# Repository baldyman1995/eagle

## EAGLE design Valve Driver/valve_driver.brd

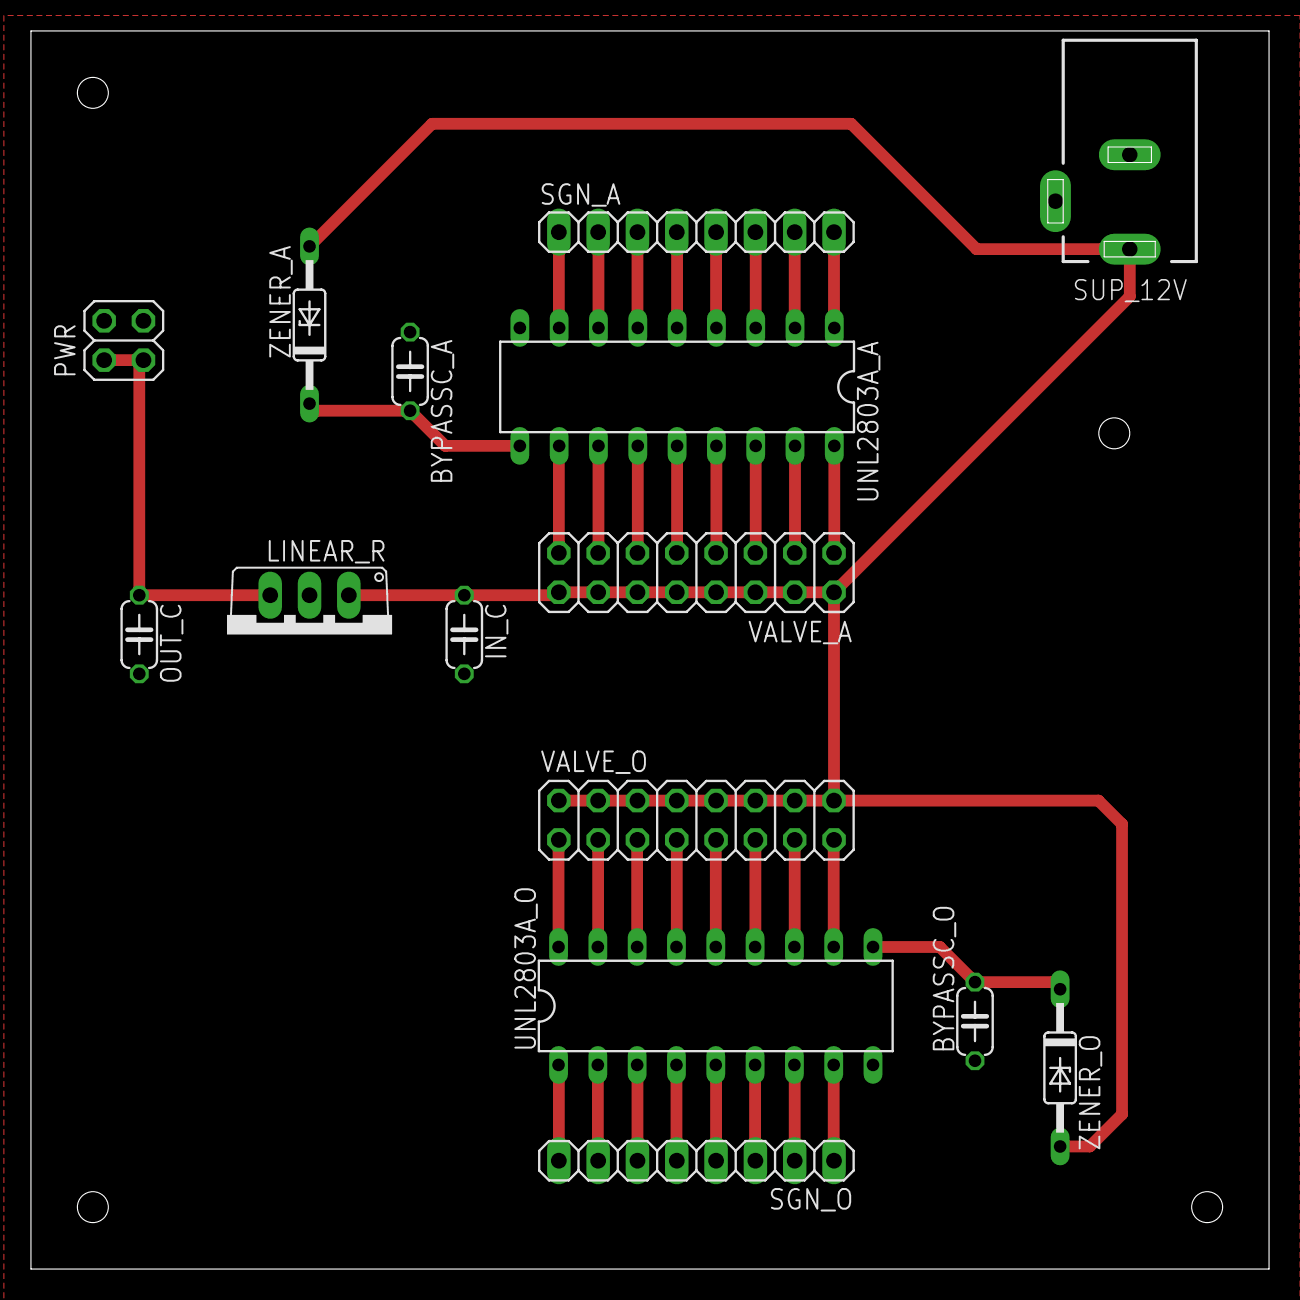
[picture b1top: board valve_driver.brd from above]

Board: 2 copper layers, 80.0 x 80.0 mm, 15 parts (0 on the bottom side), 37 nets.

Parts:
BYPASSC_A: 0.33u; C050-024X044
BYPASSC_O: 0.33u; C050-024X044
IN_C: 0.33u; C050-024X044
LINEAR_R: 7805TV; TO220V
OUT_C: 0.1u; C050-024X044
PWR: 2X02
SGN_A: 1X08
SGN_O: 1X08
SUP_12V: DCJ0202
UNL2803A_A, UNL2803A_O: DIL18
VALVE_A: 2X08
VALVE_O: 2X08
ZENER_A: 18v; DO35Z10
ZENER_O: 18v; DO35Z10

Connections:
COM1: BYPASSC_A.2, UNL2803A_A.10, ZENER_A.C
COM2: BYPASSC_O.2, UNL2803A_O.10, ZENER_O.C
GND: BYPASSC_A.1, BYPASSC_O.1, IN_C.2, LINEAR_R.2, OUT_C.2, PWR.3, PWR.4, SUP_12V.2, SUP_12V.3, UNL2803A_A.9, UNL2803A_O.9
unnamed: UNL2803A_O.11, VALVE_O.15
unnamed: UNL2803A_O.12, VALVE_O.13
unnamed: UNL2803A_O.13, VALVE_O.11
unnamed: UNL2803A_O.14, VALVE_O.9
unnamed: UNL2803A_O.15, VALVE_O.7
unnamed: UNL2803A_O.16, VALVE_O.5
unnamed: UNL2803A_O.17, VALVE_O.3
unnamed: UNL2803A_O.18, VALVE_O.1
unnamed: SGN_O.1, UNL2803A_O.8
unnamed: SGN_O.2, UNL2803A_O.7
unnamed: SGN_O.3, UNL2803A_O.6
unnamed: SGN_O.4, UNL2803A_O.5
unnamed: SGN_O.5, UNL2803A_O.4
unnamed: SGN_O.6, UNL2803A_O.3
unnamed: SGN_O.7, UNL2803A_O.2
unnamed: SGN_O.8, UNL2803A_O.1
unnamed: UNL2803A_A.11, VALVE_A.15
unnamed: UNL2803A_A.12, VALVE_A.13
unnamed: UNL2803A_A.13, VALVE_A.11
unnamed: UNL2803A_A.14, VALVE_A.9
unnamed: UNL2803A_A.15, VALVE_A.7
unnamed: UNL2803A_A.16, VALVE_A.5
unnamed: UNL2803A_A.17, VALVE_A.3
unnamed: UNL2803A_A.18, VALVE_A.1
unnamed: SGN_A.1, UNL2803A_A.8
unnamed: SGN_A.2, UNL2803A_A.7
unnamed: SGN_A.3, UNL2803A_A.6
unnamed: SGN_A.4, UNL2803A_A.5
unnamed: SGN_A.5, UNL2803A_A.4
unnamed: SGN_A.6, UNL2803A_A.3
unnamed: SGN_A.7, UNL2803A_A.2
unnamed: SGN_A.8, UNL2803A_A.1
VCCH: IN_C.1, LINEAR_R.1, SUP_12V.1, VALVE_A.2, VALVE_A.4, VALVE_A.6, VALVE_A.8, VALVE_A.10, VALVE_A.12, VALVE_A.14, VALVE_A.16, VALVE_O.2, VALVE_O.4, VALVE_O.6, VALVE_O.8, VALVE_O.10, VALVE_O.12, VALVE_O.14, VALVE_O.16, ZENER_A.A, ZENER_O.A
VCCL: LINEAR_R.3, OUT_C.1, PWR.1, PWR.2

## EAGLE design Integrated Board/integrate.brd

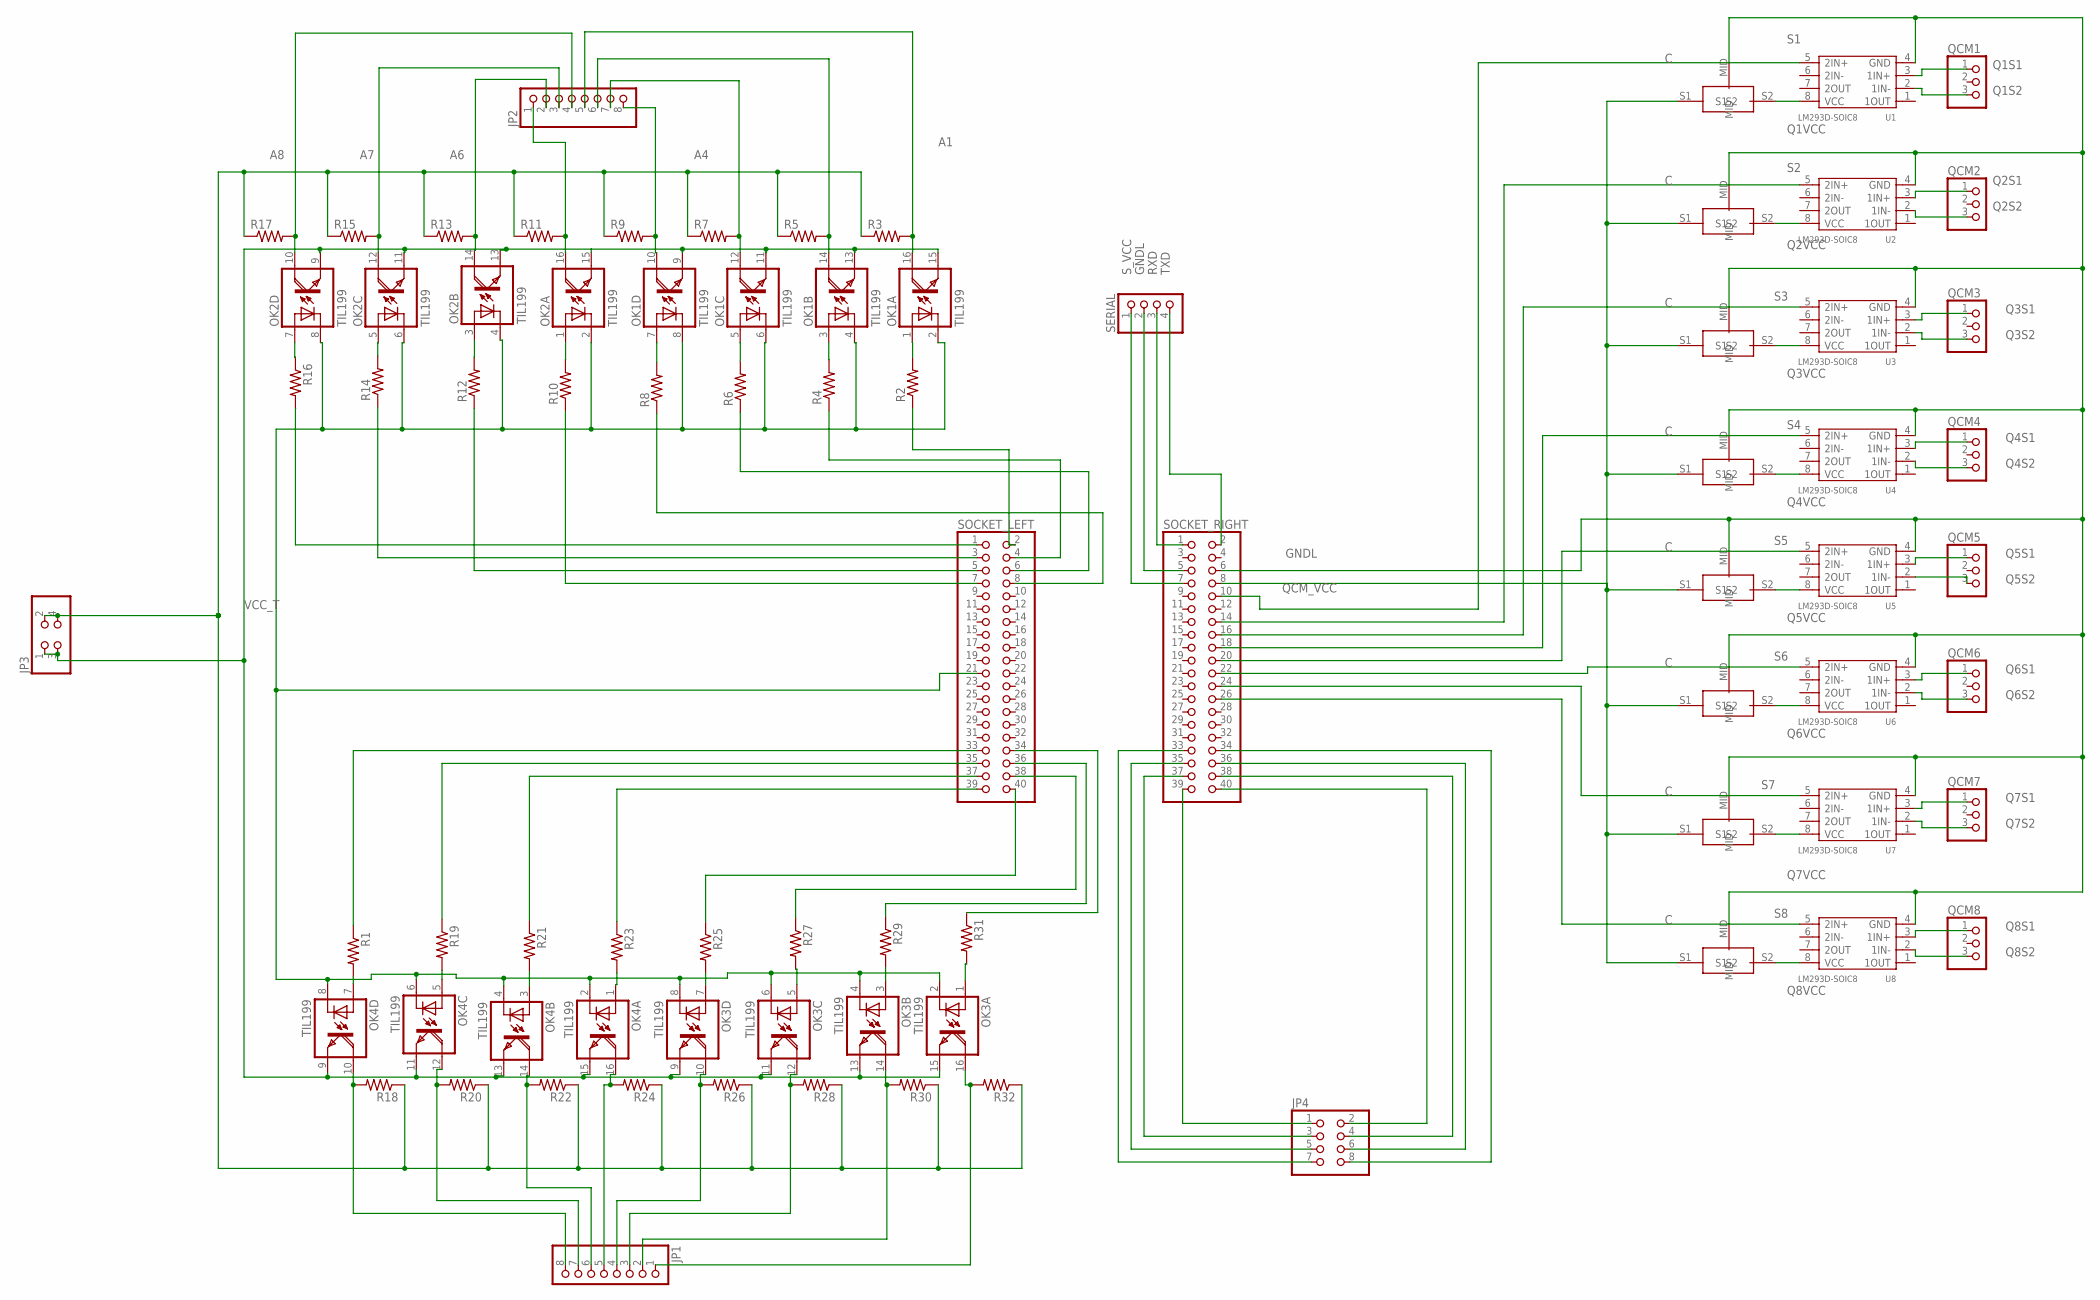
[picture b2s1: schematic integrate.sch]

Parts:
JP1, JP2: PINHD-1X8; 1X08
JP3: PINHD-2X2; 2X02
JP4: PINHD-2X4; 2X04
OK1, OK2, OK3, OK4: TIL199; DIL16
OSCILLATOR3, OSCILLATOR4, OSCILLATOR5, OSCILLATOR6, OSCILLATOR7, OSCILLATOR8, OSCILLATOR9, OSCILLATOR10: CSMD; C
QCM1, QCM2, QCM3, QCM4, QCM5, QCM6, QCM7, QCM8: PINHD-1X3; 1X03
R1, R2, R3, R4, R5, R6, R7, R8, R9, R10, R11, R12, R13, R14, R15, R16, R17, R18, R19, R20, R21, R22, R23, R24, R25, R26, R27, R28, R29, R30, R31, R32: R-US_0204/7; 0204/7
SERIAL: PINHD-1X4; 1X04
SOCKET_LEFT: PINHD-2X20; 2X20
SOCKET_RIGHT: PINHD-2X20; 2X20
U1, U2, U3, U4, U5, U6, U7, U8: LM293D-SOIC8; SOIC8-1.27-5X4MM

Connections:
A1: JP2.5, OK1.16 (COL), R3.2
A4: JP2.8, OK1.10 (COL), R9.2
A6: JP2.2, OK2.14 (COL), R13.2
A7: JP2.3, OK2.12 (COL), R15.2
A8: JP2.4, OK2.10 (COL), R17.2
GNDH: JP3.1, JP3.3, OK1.9 (EMI), OK1.11 (EMI), OK1.13 (EMI), OK1.15 (EMI), OK2.9 (EMI), OK2.11 (EMI), OK2.13 (EMI), OK2.15 (EMI), OK3.9 (EMI), OK3.11 (EMI), OK3.13 (EMI), OK3.15 (EMI), OK4.9 (EMI), OK4.11 (EMI), OK4.13 (EMI), OK4.15 (EMI)
GNDL: OK1.2 (C), OK1.4 (C), OK1.6 (C), OK1.8 (C), OK2.2 (C), OK2.4 (C), OK2.6 (C), OK2.8 (C), OK3.2 (C), OK3.4 (C), OK3.6 (C), OK3.8 (C), OK4.2 (C), OK4.4 (C), OK4.6 (C), OK4.8 (C), OSCILLATOR3.MID, OSCILLATOR4.MID, OSCILLATOR5.MID, OSCILLATOR6.MID, OSCILLATOR7.MID, OSCILLATOR8.MID, OSCILLATOR9.MID, OSCILLATOR10.MID, SERIAL.2, SOCKET_LEFT.21, SOCKET_RIGHT.5, SOCKET_RIGHT.6, U1.4 (GND), U2.4 (GND), U3.4 (GND), U4.4 (GND), U5.4 (GND), U6.4 (GND), U7.4 (GND), U8.4 (GND)
unnamed: JP4.8, SOCKET_RIGHT.34
unnamed: R10.1, SOCKET_LEFT.7
unnamed: JP4.6, SOCKET_RIGHT.36
unnamed: JP4.4, SOCKET_RIGHT.38
unnamed: JP4.2, SOCKET_RIGHT.40
unnamed: OK4.7 (A), R1.2
unnamed: JP4.5, SOCKET_RIGHT.35
unnamed: JP4.3, SOCKET_RIGHT.37
unnamed: JP4.1, SOCKET_RIGHT.39
unnamed: R12.1, SOCKET_LEFT.5
unnamed: R14.1, SOCKET_LEFT.3
unnamed: R16.2, SOCKET_LEFT.1
unnamed: OK2.7 (A), R16.1
unnamed: OK2.5 (A), R14.2
unnamed: OK2.3 (A), R12.2
unnamed: OK2.1 (A), R10.2
unnamed: R2.1, SOCKET_LEFT.2
unnamed: OK1.7 (A), R8.2
unnamed: OK1.1 (A), R2.2
unnamed: OK1.3 (A), R4.2
unnamed: OK1.5 (A), R6.2
unnamed: JP2.6, OK1.14 (COL), R5.2
unnamed: JP2.7, OK1.12 (COL), R7.2
unnamed: JP2.1, OK2.16 (COL), R11.2
unnamed: R4.1, SOCKET_LEFT.4
unnamed: R6.1, SOCKET_LEFT.6
unnamed: R8.1, SOCKET_LEFT.8
unnamed: OK4.5 (A), R19.2
unnamed: OK4.3 (A), R21.2
unnamed: OK4.1 (A), R23.2
unnamed: OK3.7 (A), R25.2
unnamed: OK3.5 (A), R27.2
unnamed: OK3.3 (A), R29.2
unnamed: OK3.1 (A), R31.2
unnamed: JP1.1, OK3.16 (COL), R32.2
unnamed: JP4.7, SOCKET_RIGHT.33
unnamed: JP1.2, OK3.14 (COL), R30.2
unnamed: JP1.3, OK3.12 (COL), R28.2
unnamed: JP1.4, OK3.10 (COL), R26.2
unnamed: JP1.5, OK4.16 (COL), R24.2
unnamed: JP1.6, OK4.14 (COL), R22.2
unnamed: JP1.7, OK4.12 (COL), R20.2
unnamed: JP1.8, OK4.10 (COL), R18.2
unnamed: R31.1, SOCKET_LEFT.34
unnamed: R29.1, SOCKET_LEFT.36
unnamed: R27.1, SOCKET_LEFT.38
unnamed: R25.1, SOCKET_LEFT.40
unnamed: R23.1, SOCKET_LEFT.39
unnamed: R21.1, SOCKET_LEFT.37
unnamed: R19.1, SOCKET_LEFT.35
unnamed: R1.1, SOCKET_LEFT.33
Q1S1: QCM1.1, U1.3 (1IN+)
Q1S2: QCM1.3, U1.2 (1IN-)
Q1VCC: OSCILLATOR3.S2, U1.8 (VCC)
Q2S1: QCM2.1, U2.3 (1IN+)
Q2S2: QCM2.3, U2.2 (1IN-)
Q2VCC: OSCILLATOR4.S2, U2.8 (VCC)
Q3S1: QCM3.1, U3.3 (1IN+)
Q3S2: QCM3.3, U3.2 (1IN-)
Q3VCC: OSCILLATOR5.S2, U3.8 (VCC)
Q4S1: QCM4.1, U4.3 (1IN+)
Q4S2: QCM4.3, U4.2 (1IN-)
Q4VCC: OSCILLATOR6.S2, U4.8 (VCC)
Q5S1: QCM5.1, U5.3 (1IN+)
Q5S2: QCM5.3, U5.2 (1IN-)
Q5VCC: OSCILLATOR7.S2, U5.8 (VCC)
Q6S1: QCM6.1, U6.3 (1IN+)
Q6S2: QCM6.3, U6.2 (1IN-)
Q6VCC: OSCILLATOR8.S2, U6.8 (VCC)
Q7S1: QCM7.1, U7.3 (1IN+)
Q7S2: QCM7.3, U7.2 (1IN-)
Q7VCC: OSCILLATOR9.S2, U7.8 (VCC)
Q8S1: QCM8.1, U8.3 (1IN+)
Q8S2: QCM8.3, U8.2 (1IN-)
Q8VCC: OSCILLATOR10.S2, U8.8 (VCC)
QCM_VCC: OSCILLATOR3.S1, OSCILLATOR4.S1, OSCILLATOR5.S1, OSCILLATOR6.S1, OSCILLATOR7.S1, OSCILLATOR8.S1, OSCILLATOR9.S1, OSCILLATOR10.S1, SOCKET_RIGHT.8
RXD: SERIAL.3, SOCKET_RIGHT.1
S1: SOCKET_RIGHT.10, SOCKET_RIGHT.12, U1.5 (2IN+)
S2: SOCKET_RIGHT.14, U2.5 (2IN+)
S3: SOCKET_RIGHT.16, U3.5 (2IN+)
S4: SOCKET_RIGHT.18, U4.5 (2IN+)
S5: SOCKET_RIGHT.20, U5.5 (2IN+)
S6: SOCKET_RIGHT.22, U6.5 (2IN+)
S7: SOCKET_RIGHT.24, U7.5 (2IN+)
S8: SOCKET_RIGHT.26, U8.5 (2IN+)
S_VCC: SERIAL.1, SOCKET_RIGHT.7
TXD: SERIAL.4, SOCKET_RIGHT.2
VCC_T: JP3.2, JP3.4, R3.1, R5.1, R7.1, R9.1, R11.1, R13.1, R15.1, R17.1, R18.1, R20.1, R22.1, R24.1, R26.1, R28.1, R30.1, R32.1

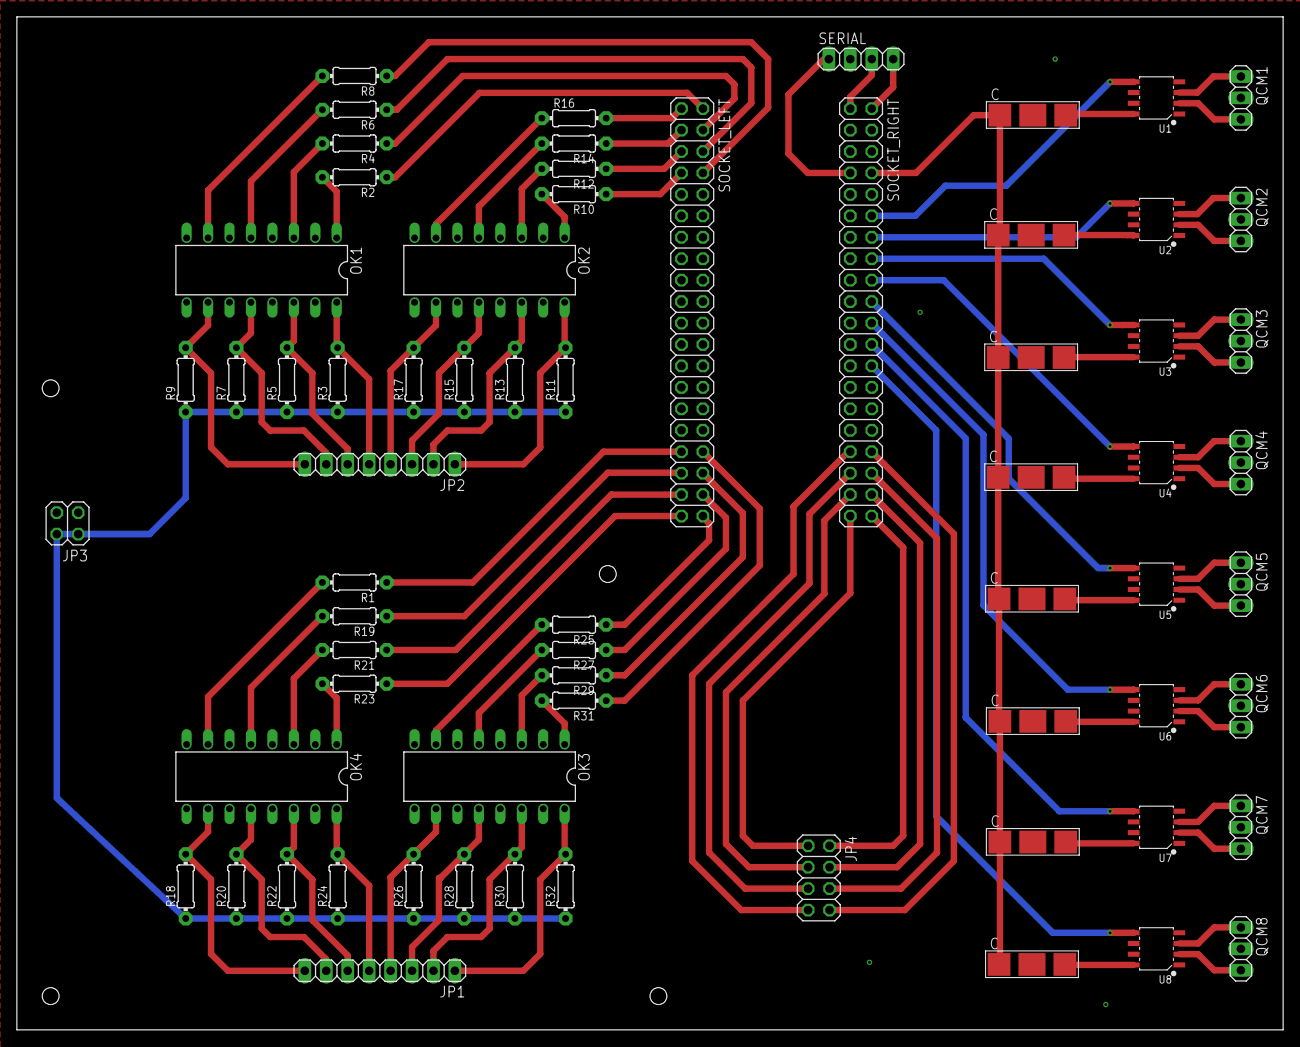
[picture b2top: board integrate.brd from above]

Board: 2 copper layers, 150.0 x 120.0 mm, 67 parts (0 on the bottom side), 95 nets.

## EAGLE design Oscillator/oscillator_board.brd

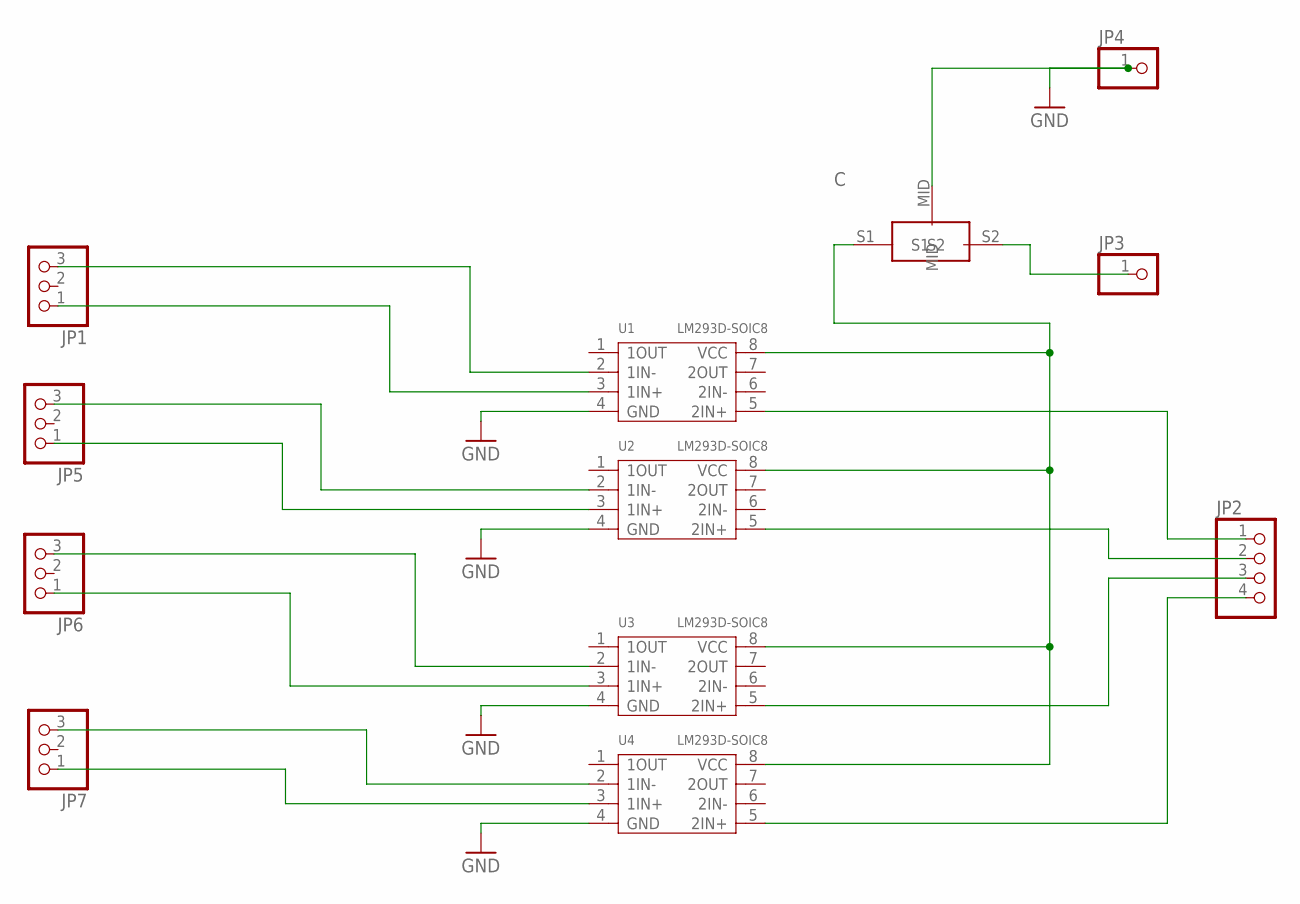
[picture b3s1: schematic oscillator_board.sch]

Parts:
JP1, JP5, JP6, JP7: PINHD-1X3; 1X03
JP2: PINHD-1X4; 1X04
JP3, JP4: PINHD-1X1; 1X01
OSCILLATOR1: CSMD; C
U1, U2, U3, U4: LM293D-SOIC8; SOIC8-1.27-5X4MM

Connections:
GND: JP4.1, OSCILLATOR1.MID, U1.4 (GND), U2.4 (GND), U3.4 (GND), U4.4 (GND)
unnamed: JP1.3, U1.2 (1IN-)
unnamed: JP1.1, U1.3 (1IN+)
unnamed: JP5.3, U2.2 (1IN-)
unnamed: JP5.1, U2.3 (1IN+)
unnamed: JP6.3, U3.2 (1IN-)
unnamed: JP6.1, U3.3 (1IN+)
unnamed: JP7.3, U4.2 (1IN-)
unnamed: JP7.1, U4.3 (1IN+)
unnamed: JP2.4, U4.5 (2IN+)
unnamed: JP2.3, U3.5 (2IN+)
unnamed: JP2.2, U2.5 (2IN+)
unnamed: JP2.1, U1.5 (2IN+)
unnamed: JP3.1, OSCILLATOR1.S2
VCC: OSCILLATOR1.S1, U1.8 (VCC), U2.8 (VCC), U3.8 (VCC), U4.8 (VCC)

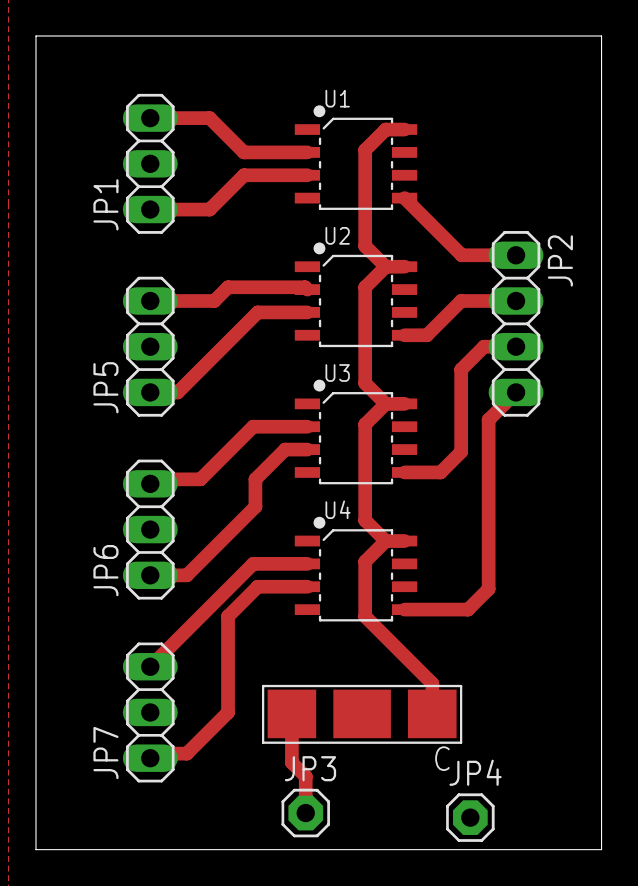
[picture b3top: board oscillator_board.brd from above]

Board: 2 copper layers, 31.4 x 45.2 mm, 12 parts (0 on the bottom side), 15 nets.

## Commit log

2018-07-11 change-of-jack
2018-07-12 20180712-edited-version
2018-07-12 20180712-change-pin
    change ch1's pin to right(10):
    right(11,12) is not avaliable
2018-07-12 Revert "Merge branch 'master' of https://github.com/baldyman1995/eagle"
    This reverts commit 490f2b321465501f62e6cee94e508c15579ea0af, reversing
    changes made to fb38f18733497d936434fddb3c409504ab7d6048.
2018-07-12 Revert "20180712-change-pin"
    This reverts commit fb38f18733497d936434fddb3c409504ab7d6048.
2018-07-12 Unkown-change
2018-07-19 20180719-Fix-problem-for-LVB
    1. OSC part: left top 6th channel cannot be arranged, change pin to left top 5th
    2.change the area of HVB
2018-07-23 20180723-fixed-small-mistake
    on valve driver board, the regulated vcc port is not connected. Now it is.
2018-10-03 20181003-null
    null
